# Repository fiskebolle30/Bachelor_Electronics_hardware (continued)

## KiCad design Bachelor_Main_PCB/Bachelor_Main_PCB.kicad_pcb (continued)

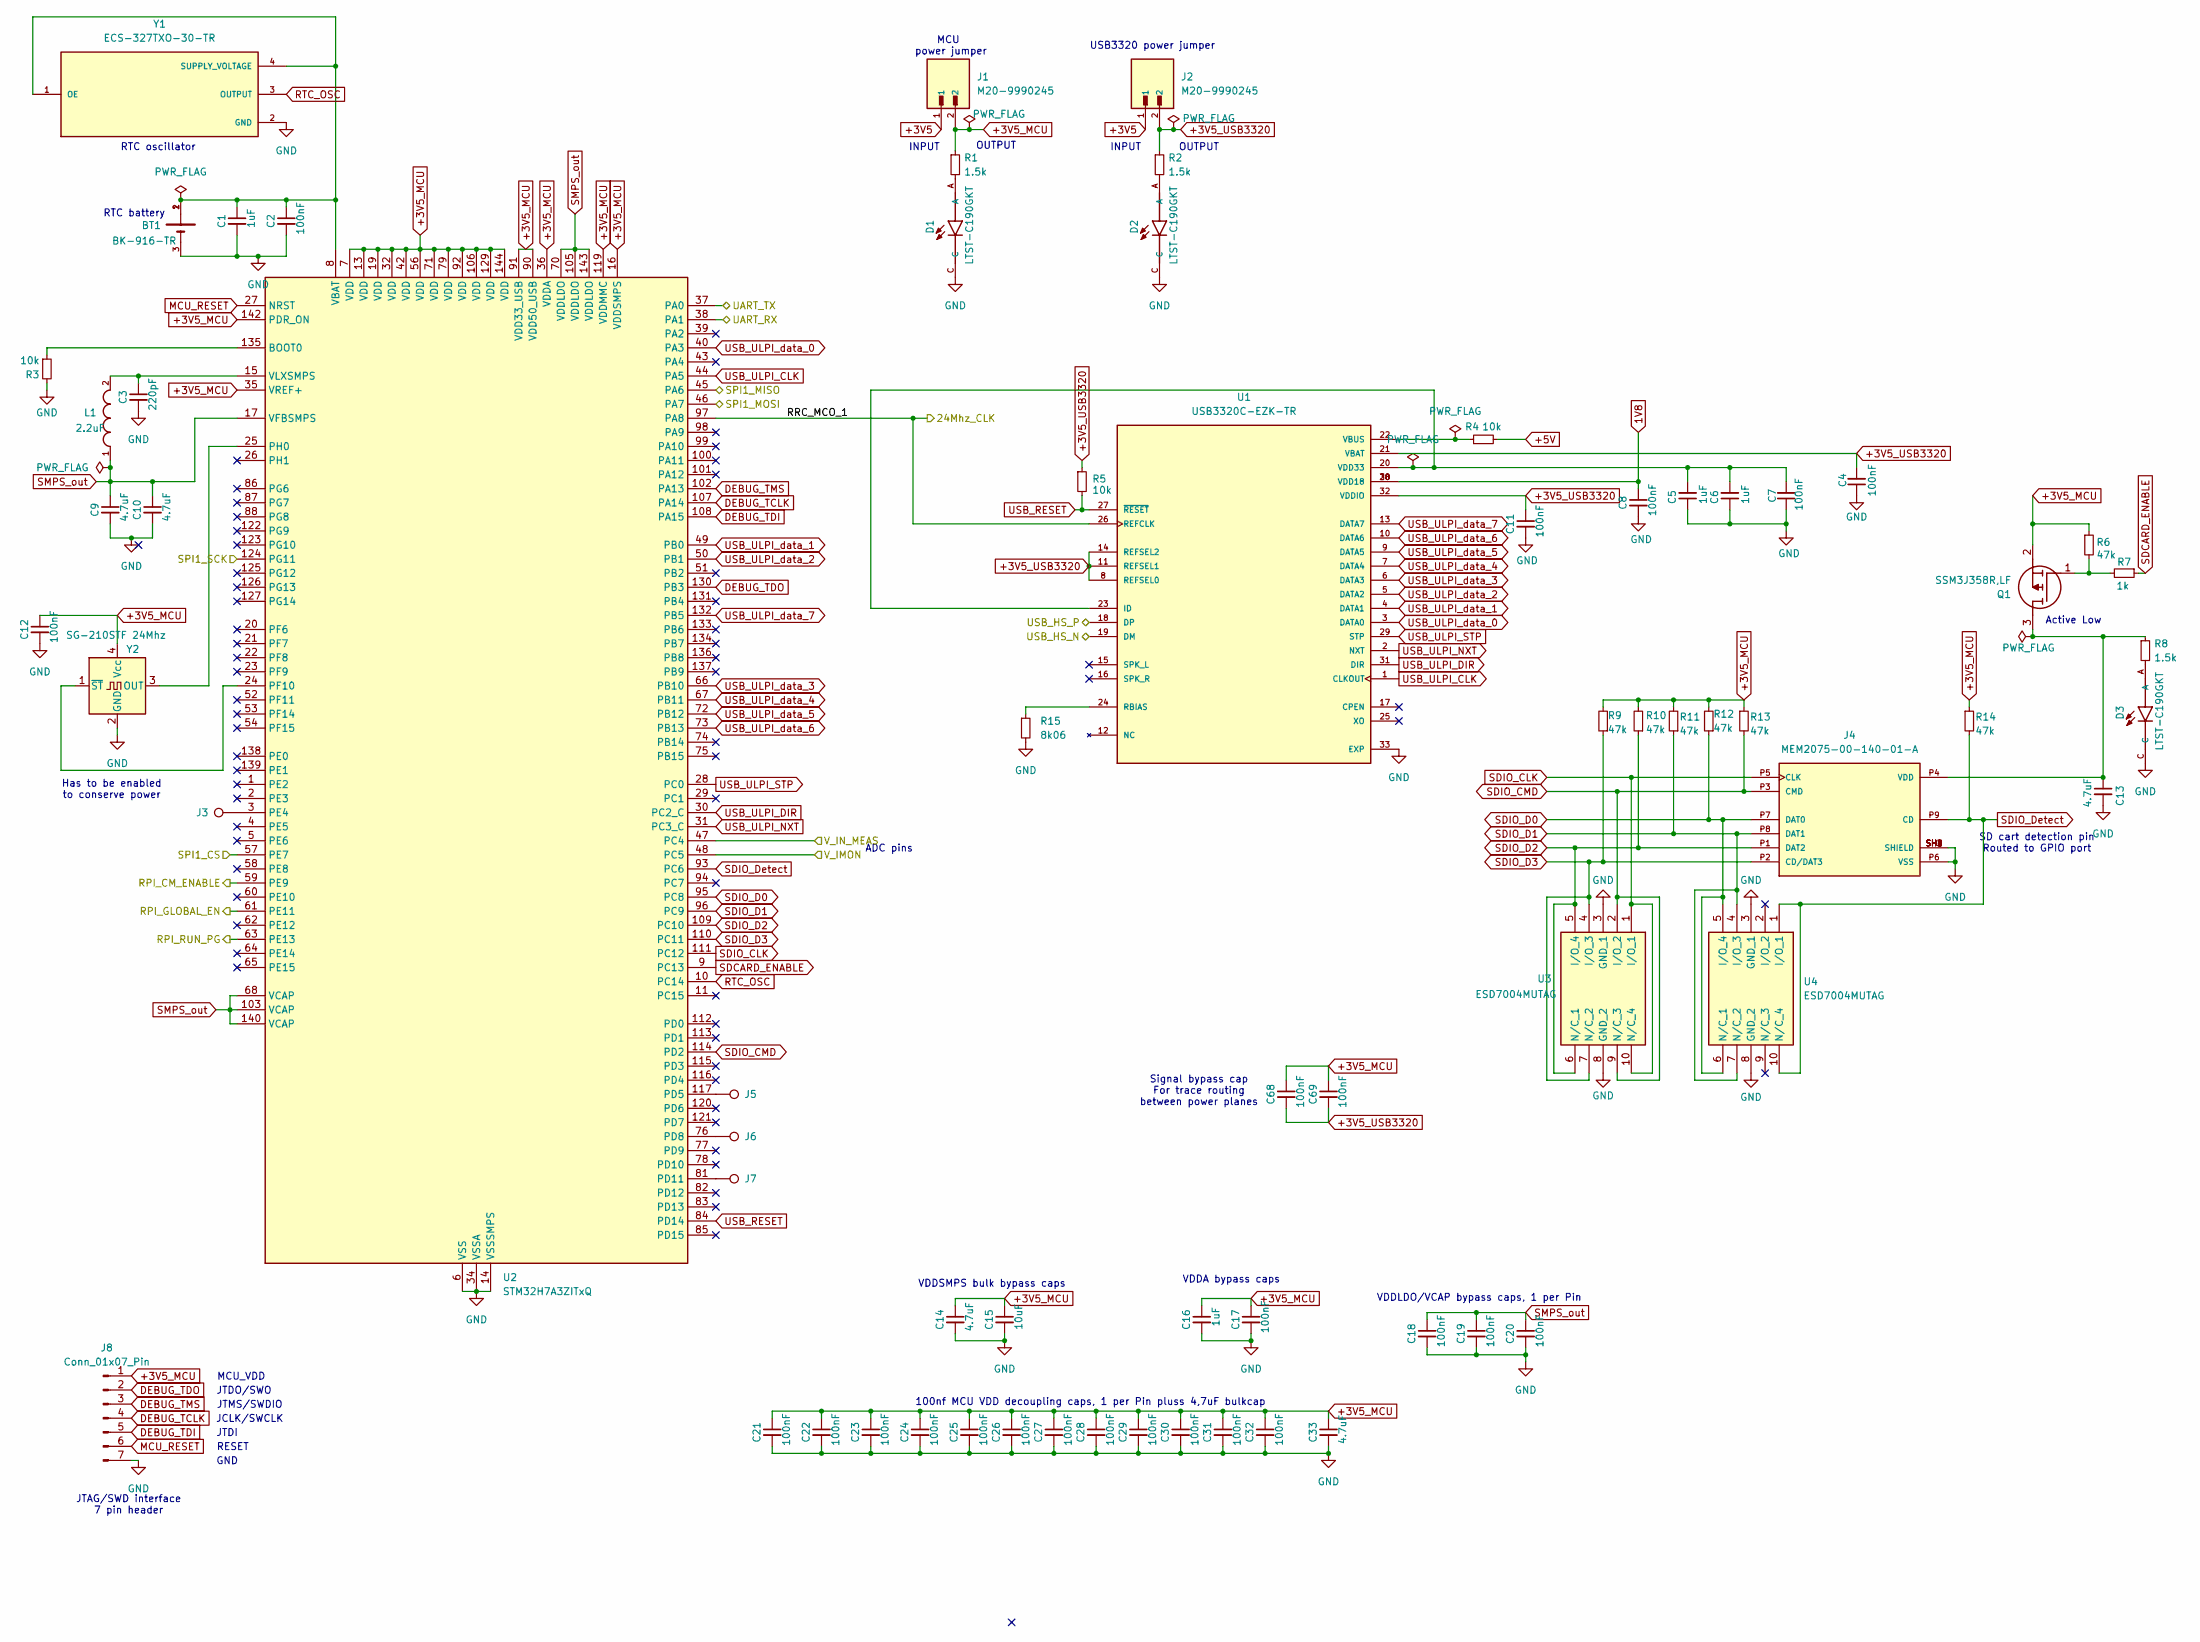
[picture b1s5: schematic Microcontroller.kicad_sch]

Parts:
BT1: BK-916-TR; BAT_BK-916-TR; PARTREV A
C1, C5, C6, C16: 1uF; C_0603_1608Metric; Voltage rating 16v; Part-no CL10B105KO8NNNC
C2, C4, C7, C8, C11, C12, C17, C18, C19, C20, C21, C22, C23, C24, C25, C26, C27, C28, C29, C30, C31, C32, C68, C69: 100nF; C_0603_1608Metric; Voltage rating 50v; Part-no CL10B104KB8NNWC
C3: 220pF; C_0603_1608Metric; Voltage rating 50v; Part-no C0603C221J5GAC7411
C9, C10, C13, C14, C33: 4.7uF; C_0805_2012Metric; Voltage rating 25v; Part-no CL21A475KAQNNNE
C15: 10uF; C_1206_3216Metric; Voltage rating 50v; Part-no CL31B106KBHNNNE
D1, D2, D3: LTST-C190GKT; LEDM1608X80; Part-no LTST-C190GKT
J1, J2: M20-9990245; HARWIN_M20-9990245; PARTREV 14
J3, J5, J6, J7: TestPoint_Pad_D1.0mm
J4: MEM2075-00-140-01-A; GCT_MEM2075-00-140-01-A; PARTREV A
J8: Conn_01x07_Pin; PinHeader_1x07_P2.54mm_Vertical
L1: 2.2uF; INDC2520X120N; Part-no DFE252012P-2R2M=P2
Q1: SSM3J358R,LF; SOTFL95P240X88-3N; Manufacturer_Part_Number SSM3J358R,LF; Mouser Part Number 757-SSM3J358RLF
R1, R2, R8: 1.5k; R_0603_1608Metric
R3, R4, R5: 10k; R_0603_1608Metric; Part-no RC0603FR-0710KL
R6, R9, R10, R11, R12, R13, R14: 47k; R_0603_1608Metric
R7: 1k; R_0603_1608Metric
R15: 8k06; R_0603_1608Metric
U1: USB3320C-EZK-TR; QFN50P500X500X100-33N; PARTREV 05-31-16
U2: STM32H7A3ZITxQ; LQFP-144_20x20mm_P0.5mm; Part-no STM32H7A3ZIT6Q
U3, U4: ESD7004MUTAG; UDFN10_CASE_517BB; Manufacturer_Part_Number ESD7004MUTAG; Mouser Part Number 863-ESD7004MUTAG
Y1: ECS-327TXO-30-TR; OSC_ECS-327TXO-30-TR; PARTREV Rev.2019
Y2: SG-210STF 24Mhz; Oscillator_SMD_SeikoEpson_SG210-4Pin_2.5x2.0mm; Part-no SG-210STF 24Mhz

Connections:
1V8: C8.1, U1.28 (VDD18), U1.30 (VDD18); also elsewhere on the board
+3V5: J1.1, J2.1; also elsewhere on the board
+3V5_MCU: C12.1, C14.1, C15.1, C16.1, C17.1, C21.1, C22.1, C23.1, C24.1, C25.1, C26.1, C27.1, C28.1, C29.1, C30.1, C31.1, C32.1, C33.1, C68.1, C69.1, J1.2, J8.1, Q1.2 (S), R1.1, R6.1, R9.2, R10.2, R11.2, R12.2, R13.1, R14.1, U2.7 (VDD), U2.13 (VDD), U2.16 (VDDSMPS), U2.19 (VDD), U2.32 (VDD), U2.35 (VREF+), U2.36 (VDDA), U2.42 (VDD), U2.56 (VDD), U2.71 (VDD), U2.79 (VDD), U2.90 (VDD50_USB), U2.91 (VDD33_USB), U2.92 (VDD), U2.106 (VDD), U2.119 (VDDMMC), U2.129 (VDD), U2.142 (PDR_ON), U2.144 (VDD), Y2.4 (Vcc)
+3V5_USB3320: C4.2, C11.1, C68.2, C69.2, J2.2, R2.1, R5.1, U1.8 (REFSEL0), U1.11 (REFSEL1), U1.14 (REFSEL2), U1.21 (VBAT), U1.32 (VDDIO)
+5V: R4.2; also elsewhere on the board
/Microcontroller/RPI_CM_ENABLE: U2.59 (PE9); also elsewhere on the board
/Microcontroller/RPI_GLOBAL_EN: U2.61 (PE11); also elsewhere on the board
/Microcontroller/RPI_RUN_PG: U2.63 (PE13); also elsewhere on the board
/Microcontroller/RRC_MCO_1: U1.26 (REFCLK), U2.97 (PA8); also elsewhere on the board
/Microcontroller/UART_RX: U2.38 (PA1); also elsewhere on the board
/Microcontroller/UART_TX: U2.37 (PA0); also elsewhere on the board
/Microcontroller/USB_HS_N: U1.19 (DM); also elsewhere on the board
/Microcontroller/USB_HS_P: U1.18 (DP); also elsewhere on the board
/Microcontroller/V_IMON: U2.48 (PC5); also elsewhere on the board
/Microcontroller/V_IN_MEAS: U2.47 (PC4); also elsewhere on the board
DEBUG_TCLK: J8.4, U2.107 (PA14)
DEBUG_TDI: J8.5, U2.108 (PA15)
DEBUG_TDO: J8.2, U2.130 (PB3)
DEBUG_TMS: J8.3, U2.102 (PA13)
GND: BT1.3, C1.2, C2.2, C3.2, C4.1, C5.1, C6.1, C7.1, C8.2, C9.2, C10.2, C11.2, C12.2, C13.2, C14.2, C15.2, C16.2, C17.2, C18.2, C19.2, C20.2, C21.2, C22.2, C23.2, C24.2, C25.2, C26.2, C27.2, C28.2, C29.2, C30.2, C31.2, C32.2, C33.2, D1.C, D2.C, D3.C, J4.P6 (VSS), J4.SH1 (SHIELD), J4.SH2 (SHIELD), J4.SH3 (SHIELD), J4.SH4 (SHIELD), J8.7, R3.2, R15.2, U1.33 (EXP), U2.6 (VSS), U2.12 (VSS), U2.14 (VSSSMPS), U2.18 (VSS), U2.33 (VSS), U2.34 (VSSA), U2.41 (VSS), U2.55 (VSS), U2.69 (VSS), U2.80 (VSS), U2.89 (VSS), U2.104 (VSS), U2.118 (VSS), U2.128 (VSS), U2.141 (VSS), U3.3 (GND_1), U3.8 (GND_2), U4.3 (GND_1), U4.8 (GND_2), Y1.2 (GND), Y2.2 (GND); also elsewhere on the board
MCU_RESET: J8.6, U2.27 (NRST)
unnamed: D1.A, R1.2
unnamed: D2.A, R2.2
unnamed: D3.A, R8.2
unnamed: C13.1, J4.P4 (VDD), Q1.3 (D), R8.1
unnamed: Q1.1 (G), R6.2, R7.2
unnamed: C5.2, C6.2, C7.2, U1.20 (VDD33), U1.23 (ID)
unnamed: R15.1, U1.24 (RBIAS)
unnamed: R4.1, U1.22 (VBUS)
unnamed: R3.1, U2.135 (BOOT0)
unnamed: J5.1, U2.117 (PD5)
unnamed: J6.1, U2.76 (PD8)
unnamed: J7.1, U2.81 (PD11)
unnamed: J3.1, U2.3 (PE4)
unnamed: U2.24 (PF10), Y2.1 (~ST)
unnamed: U2.25 (PH0), Y2.3 (OUT)
unnamed: BT1.1, BT1.2, C1.1, C2.1, U2.8 (VBAT), Y1.1 (OE), Y1.4 (SUPPLY_VOLTAGE)
unnamed: C3.1, L1.2, U2.15 (VLXSMPS)
RTC_OSC: U2.10 (PC14), Y1.3 (OUTPUT)
SD-pin2: U2.57 (PE7); also elsewhere on the board
SD-pin3: U2.46 (PA7); also elsewhere on the board
SD-pin5: U2.124 (PG11); also elsewhere on the board
SD-pin7: U2.45 (PA6); also elsewhere on the board
SDCARD_ENABLE: R7.1, U2.9 (PC13)
SDIO_CLK: J4.P5 (CLK), U2.111 (PC12), U3.1 (I/O_1), U3.10 (N/C_4)
SDIO_CMD: J4.P3 (CMD), R13.2, U2.114 (PD2), U3.2 (I/O_2), U3.9 (N/C_3)
SDIO_D0: J4.P7 (DAT0), R12.1, U2.95 (PC8), U4.5 (I/O_4), U4.6 (N/C_1)
SDIO_D1: J4.P8 (DAT1), R11.1, U2.96 (PC9), U4.4 (I/O_3), U4.7 (N/C_2)
SDIO_D2: J4.P1 (DAT2), R10.1, U2.109 (PC10), U3.5 (I/O_4), U3.6 (N/C_1)
SDIO_D3: J4.P2 (CD/DAT3), R9.1, U2.110 (PC11), U3.4 (I/O_3), U3.7 (N/C_2)
SDIO_Detect: J4.P9 (CD), R14.2, U2.93 (PC6), U4.1 (I/O_1), U4.10 (N/C_4)
SMPS_out: C9.1, C10.1, C18.1, C19.1, C20.1, L1.1, U2.17 (VFBSMPS), U2.68 (VCAP), U2.70 (VDDLDO), U2.103 (VCAP), U2.105 (VDDLDO), U2.140 (VCAP), U2.143 (VDDLDO)
USB_RESET: R5.2, U1.27 (~RESET), U2.84 (PD14)
USB_ULPI_CLK: U1.1 (CLKOUT), U2.44 (PA5)
USB_ULPI_DIR: U1.31 (DIR), U2.30 (PC2_C)
USB_ULPI_NXT: U1.2 (NXT), U2.31 (PC3_C)
USB_ULPI_STP: U1.29 (STP), U2.28 (PC0)
USB_ULPI_data_0: U1.3 (DATA0), U2.40 (PA3)
USB_ULPI_data_1: U1.4 (DATA1), U2.49 (PB0)
USB_ULPI_data_2: U1.5 (DATA2), U2.50 (PB1)
USB_ULPI_data_3: U1.6 (DATA3), U2.66 (PB10)
USB_ULPI_data_4: U1.7 (DATA4), U2.67 (PB11)
USB_ULPI_data_5: U1.9 (DATA5), U2.72 (PB12)
USB_ULPI_data_6: U1.10 (DATA6), U2.73 (PB13)
USB_ULPI_data_7: U1.13 (DATA7), U2.132 (PB5)

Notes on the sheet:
JTDI
INPUT
SD cart detection pin Routed to GPIO port
RTC oscillator
MCU_VDD
JCLK/SWCLK
OUTPUT
ADC pins
VDDLDO/VCAP bypass caps, 1 per Pin
Signal bypass cap For trace routing between power planes
RESET
Has to be enabled to conserve power
JTDO/SWO
Active Low
100nf MCU VDD decoupling caps, 1 per Pin pluss 4,7uF bulkcap
GND
RTC battery
VDDA bypass caps
JTAG/SWD interface 7 pin header
USB3320 power jumper
MCU power jumper
VDDSMPS bulk bypass caps
JTMS/SWDIO

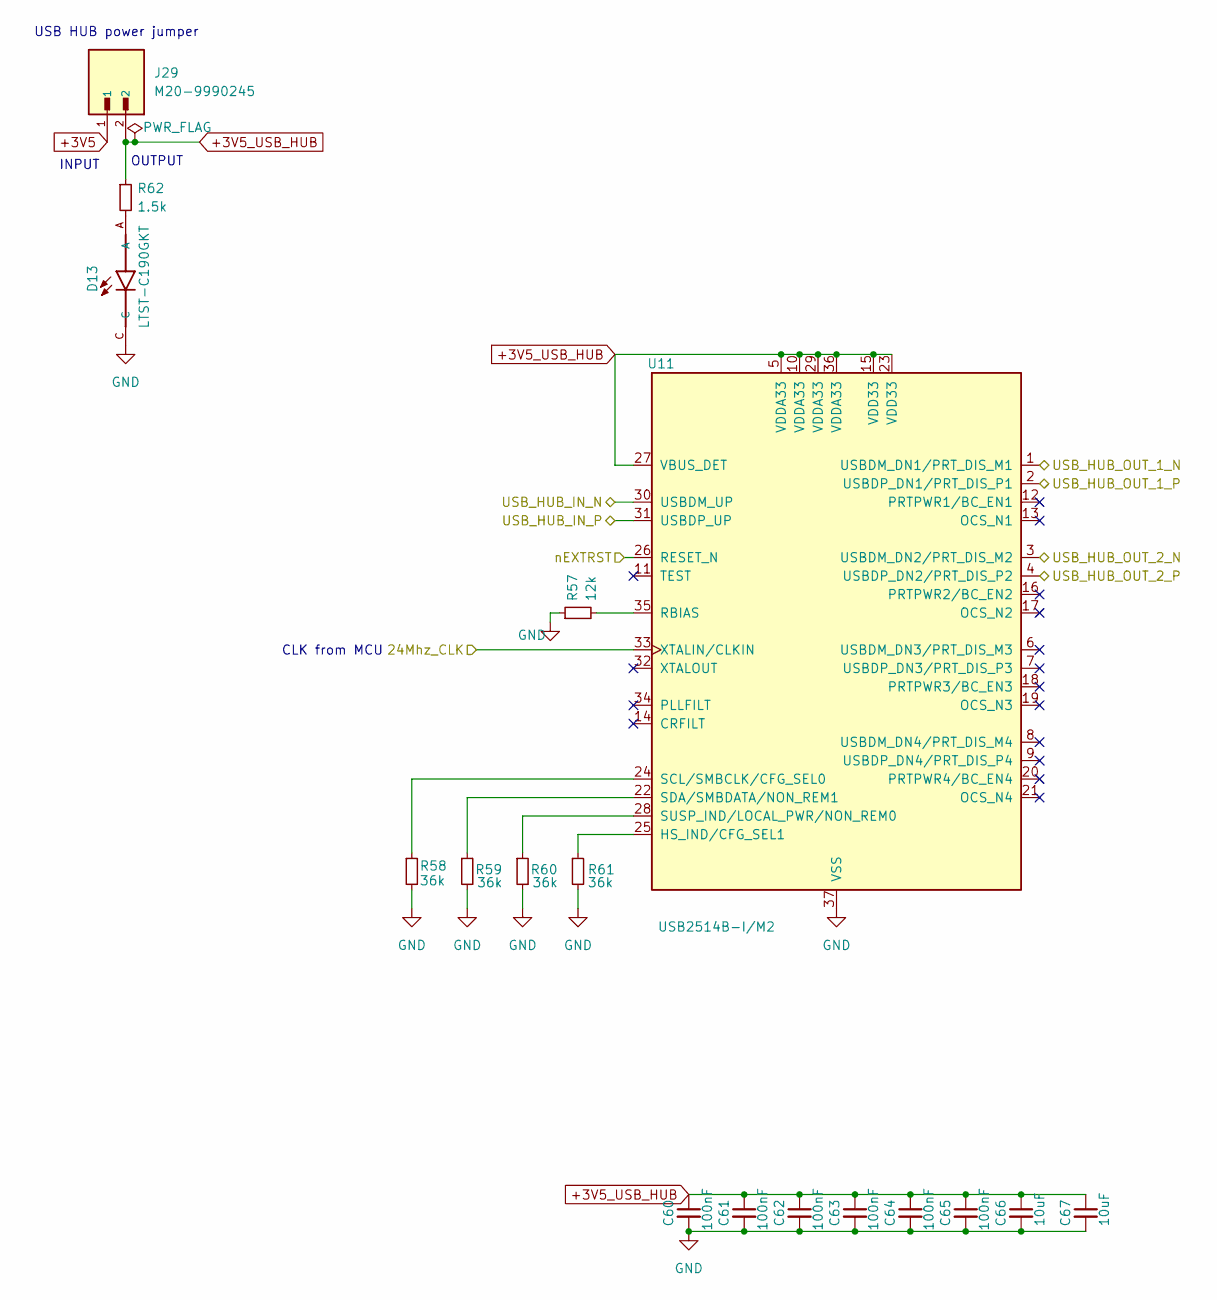
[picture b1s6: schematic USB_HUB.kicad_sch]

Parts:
C60, C61, C62, C63, C64, C65: 100nF; C_0603_1608Metric; Voltage rating 50v; Part-no CL10B104KB8NNWC
C66, C67: 10uF; C_1206_3216Metric; Voltage rating 50v; Part-no CL31B106KBHNNNE
D13: LTST-C190GKT; LEDM1608X80; Part-no LTST-C190GKT
J29: M20-9990245; HARWIN_M20-9990245; PARTREV 14
R57: 12k; R_0603_1608Metric
R58, R59, R60, R61: 36k; R_0603_1608Metric
R62: 1.5k; R_0603_1608Metric
U11: USB2514B-I/M2; QFN-36-1EP_6x6mm_P0.5mm_EP3.7x3.7mm; Part Description USB Hub Controller USB Interface 36-SQF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

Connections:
+3V5: J29.1; also elsewhere on the board
+3V5_USB_HUB: C60.1, C61.1, C62.1, C63.1, C64.1, C65.1, C66.1, C67.1, J29.2, R62.1, U11.5 (VDDA33), U11.10 (VDDA33), U11.15 (VDD33), U11.23 (VDD33), U11.27 (VBUS_DET), U11.29 (VDDA33), U11.36 (VDDA33)
/Microcontroller/RRC_MCO_1: U11.33 (XTALIN/CLKIN); also elsewhere on the board
/Microcontroller/USB_HS_N: U11.1 (USBDM_DN1/PRT_DIS_M1); also elsewhere on the board
/Microcontroller/USB_HS_P: U11.2 (USBDP_DN1/PRT_DIS_P1); also elsewhere on the board
/Raspberry Pi CM 4/USB_HS_N: U11.30 (USBDM_UP); also elsewhere on the board
/Raspberry Pi CM 4/USB_HS_P: U11.31 (USBDP_UP); also elsewhere on the board
/Raspberry Pi CM 4/nEXTRST: U11.26 (RESET_N); also elsewhere on the board
/USB Hub/USB_HUB_OUT_2_N: U11.3 (USBDM_DN2/PRT_DIS_M2); also elsewhere on the board
/USB Hub/USB_HUB_OUT_2_P: U11.4 (USBDP_DN2/PRT_DIS_P2); also elsewhere on the board
GND: C60.2, C61.2, C62.2, C63.2, C64.2, C65.2, C66.2, C67.2, D13.C, R57.1, R58.2, R59.2, R60.2, R61.2, U11.37 (VSS); also elsewhere on the board
unnamed: D13.A, R62.2
unnamed: R61.1, U11.25 (HS_IND/CFG_SEL1)
unnamed: R57.2, U11.35 (RBIAS)
unnamed: R58.1, U11.24 (SCL/SMBCLK/CFG_SEL0)
unnamed: R59.1, U11.22 (SDA/SMBDATA/NON_REM1)
unnamed: R60.1, U11.28 (SUSP_IND/LOCAL_PWR/NON_REM0)

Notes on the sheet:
CLK from MCU
OUTPUT
INPUT
USB HUB power jumper

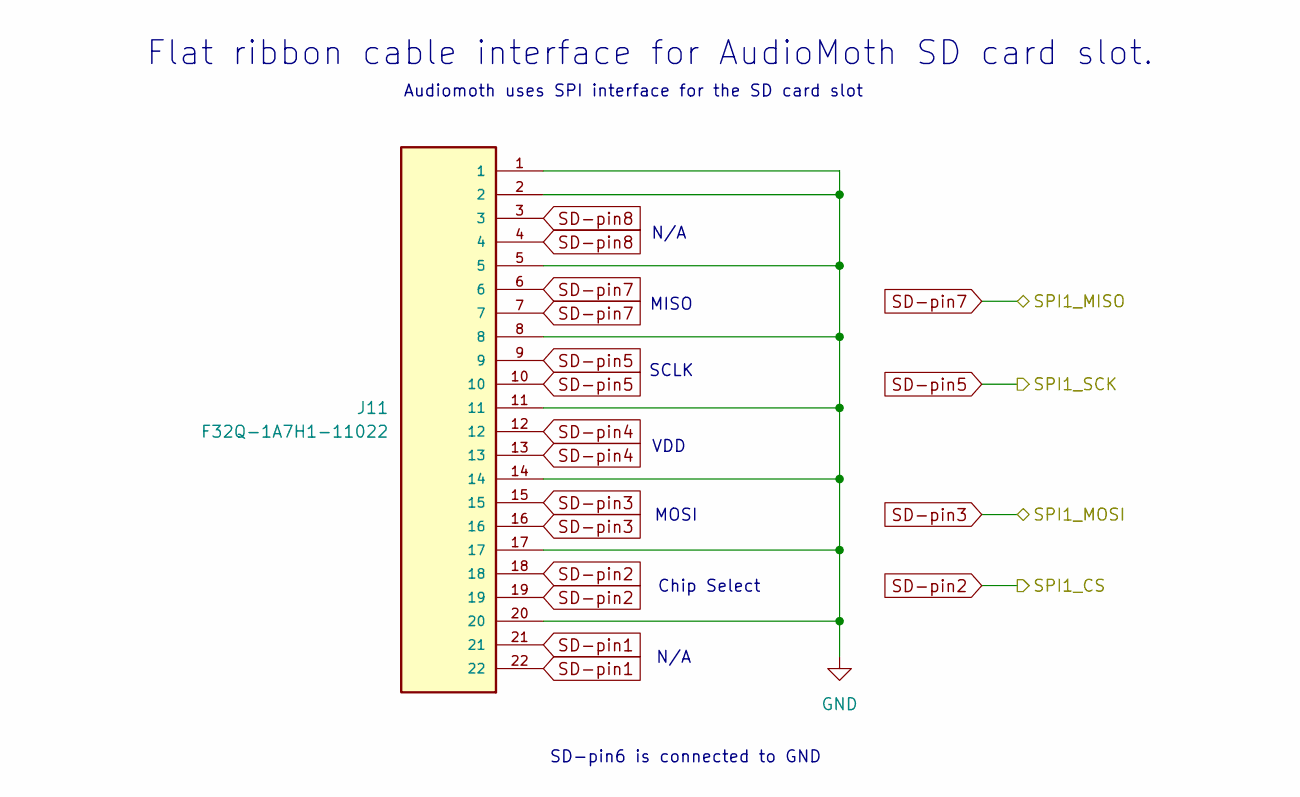
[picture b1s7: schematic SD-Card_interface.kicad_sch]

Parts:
J11: F32Q-1A7H1-11022; AMPHENOL_F32Q-1A7H1-11022; PARTREV D

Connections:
GND: J11.1, J11.2, J11.5, J11.8, J11.11, J11.14, J11.17, J11.20; also elsewhere on the board
SD-pin1: J11.21, J11.22
SD-pin2: J11.18, J11.19; also elsewhere on the board
SD-pin3: J11.15, J11.16; also elsewhere on the board
SD-pin4: J11.12, J11.13
SD-pin5: J11.9, J11.10; also elsewhere on the board
SD-pin7: J11.6, J11.7; also elsewhere on the board
SD-pin8: J11.3, J11.4

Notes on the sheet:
VDD
Flat ribbon cable interface for AudioMoth SD card slot.
SCLK
N/A
N/A
MISO
Chip Select
MOSI
Audiomoth uses SPI interface for the SD card slot
SD-pin6 is connected to GND

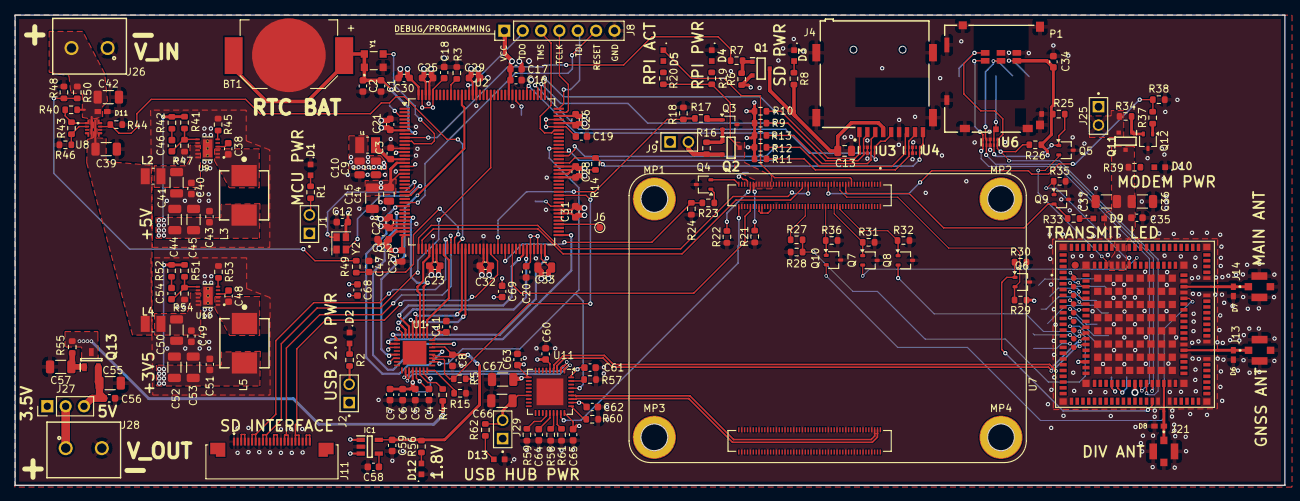
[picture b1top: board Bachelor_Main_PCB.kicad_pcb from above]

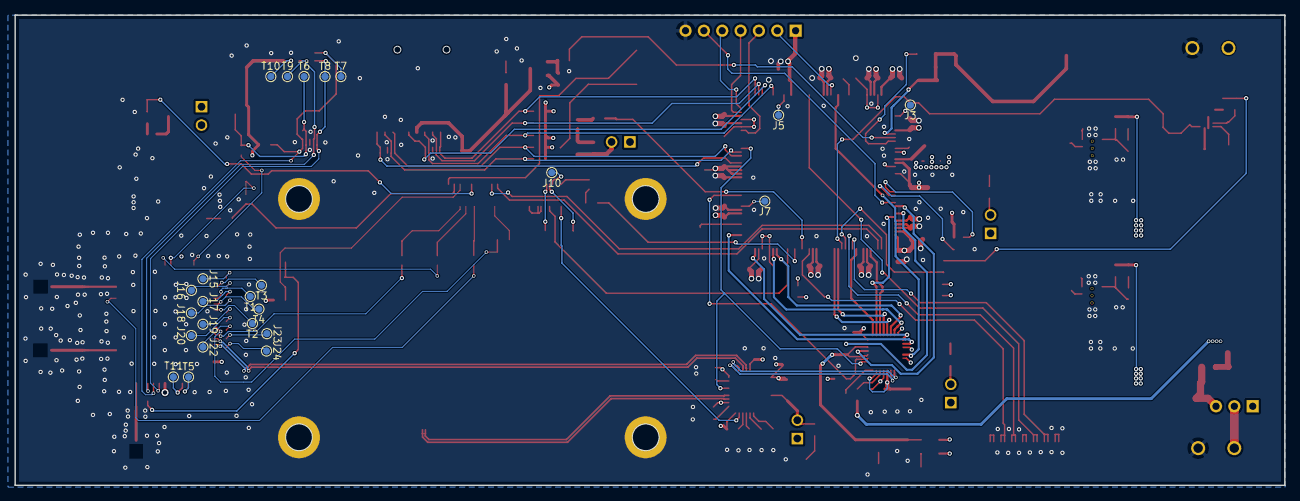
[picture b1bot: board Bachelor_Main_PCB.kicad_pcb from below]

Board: 4 copper layers, 175.8 x 65.1 mm, 224 parts (24 on the bottom side), 161 nets.

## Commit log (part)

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2025-03-04 innitial creation of KiCad project
    With 1 resistor 0603 standard size to be used
2025-03-14 Add Ribon cable connector
    F32Q-1A7H1-11022
2025-03-14 add gitignore
2025-03-14 Update gitignore removed gitignore files from repo
2025-03-14 Add RPI cm and route all Ribon cable pins correctly
2025-03-14 Updated ribon cable pins
2025-03-17 Add GND to RPI CM
2025-03-17 Add Spacers for RPI CM and created separate hierarchical sheets
2025-03-17 Add Sierra Wireless modem and 100pin RPI CM connectors
2025-03-17 Fix 100 pin RPI CM connector 3D model
    part of RPI CM 3d model now
2025-03-19 Add STM32 and 3d model. Made power suply sheet
2025-03-19 Small changes
    Just moved some components
2025-03-21 Add STM32 3D modell
2025-03-21 småtteri
2025-03-24 Add SIM card holder
2025-03-24 Add USB-Tranciever
2025-03-25 ULPI global lables
2025-03-26 Add Y1 oscillator to the USB3320
    24Mhz oscillator for the USB tranciever
2025-03-28 Add Bypass cap USB3320
2025-03-28 Routing some MCU pins
2025-03-28 Add more bypass caps
2025-03-31 Fix bypass cap routing
2025-03-31 Add Rbias resisstor to USB3320
2025-03-31 Route ID pin on USB3320, Fix 0603 footprint on resistors
2025-03-31 Add RPI_5v pin
2025-03-31 USB3320 CPEN is NC!
2025-03-31 Add USB3320 Reset pin pullup
2025-03-31 USB3320 Reset connected to PD14
2025-03-31 Route RPI USB
    PS: we need a USB hub
2025-04-01 Add 1x2header library
2025-04-01 Add MCU, USB3320 and USB_HUB power jumpers
2025-04-01 Add 2,2uF inductor to MCU
2025-04-01 Add MCU VDD caps
2025-04-01 VDDLDO add bypass caps
2025-04-02 Add more bypass caps to MCU
2025-04-02 add BK-916 rtc battery holder
2025-04-02 VDDUSB headers together
2025-04-02 PDR_on to VDD
2025-04-04 Add RTC oscillator
2025-04-04 ADD JTAG 7pin header
2025-04-07 Renamed JTAG_ pins to DEBUG_
    Due to it being both JTAG and SWD (serial wire debug)
2025-04-07 More concise labeling of DEBUG pins
2025-04-07 MODEM power connections
2025-04-07 Add MODEM testpoints
2025-04-07 Add SIM card circuit and ESD supression
2025-04-07 Fix anotation of "J" designators and routed ESD suppression on Modem
2025-04-07 ADD mosfet controls from BUGG MODEM
2025-04-07 Add all MODEM signals
2025-04-07 Add modem safe power remove
2025-04-07 Add routing between hierarchal sheets modem and RPI
2025-04-07 Switched 3,3 for 3,5_MODEM for Q11 and Q9 circuits
2025-04-08 Add MODEM_3V5_EN mosfet
    Controlls the power supply to the modem from the RPI GPIO7
2025-04-08 Change MODEM_3V5_EN mosfet to P-channel type SSM3j358R
2025-04-08 ADD MODEM_3V5_EN signal inverter
2025-04-08 Renamed wring MODEM_3V7_en to 3V5
2025-04-08 Add USB HUB of type USB2514B-i/M2
    Same as RPI CM 4 IO board
2025-04-08 Add Vcc to Y1
2025-04-08 Add 24Mhz clock to USB hub. same as USB tranciever
2025-04-08 Add HUB bypass caps
2025-04-09 ADD USBHUB Reset pin
2025-04-09 USB HUB done
2025-04-09 Fix hierarchal sheet naming for USB hub
2025-04-09 Routed Sheeets
2025-04-09 Add SD CARD pullups
2025-04-09 SD CARD ESD TVS Diodes
2025-04-09 Add cdcard to MCU connections(except detect pin)
2025-04-09 MAIN_RF TVS diode and routed SDIO_DETECT
2025-04-09 ADD UFL antenna connectors
2025-04-09 Started on PSU sheet
2025-04-11 Add GNSS antenna Connector
    Which is DNP but can be nice in future revision/ implementation
2025-04-11 add LM 73100 ideal diode
2025-04-11 Added RIMON + R1,R2,R3 to Ideal diode circuit
2025-04-12 Add RPI to MCU UART communication
2025-04-12 Add RPI power Switch MOSFET, Fix direction of power switch MOSFETs
2025-04-12 Switched RX and TX for UART connection
    so that the TX from RPI go into RX on MCU
2025-04-12 Add 1,8v regulator
    LD3985M18R
2025-04-12 updated 1,8v global lables
2025-04-12 Added text to SD audiomoth interface
2025-04-13 Make correct stackup and add 90ohm differential pair usb
2025-04-13 Made corecct 90ohm diff pair net settings
    Calculated with Saturn PCB toolkit. Width 0.23 and space 1,5
2025-04-13 Make all usb lines part of DP_90ohm nettclass
2025-04-13 55ohm ULPI Net made and assigned
2025-04-13 Add RPI CM enable pin to MCU sheet
2025-04-13 Add SDcard enable VCC pin with PMOS
2025-04-13 Fixed schematic of SDcard enable pin
2025-04-14 Add audiomoth to MCU SPI
2025-04-14 Add Vin sampling and route V_IN and V_IMON to MCU sheet
2025-04-14 add PC4 and PC5 as V_IN and V_IMON
2025-04-14 Add LMR51450 switch mode regulator.
2025-04-14 Remove RPI CM power on mosfet. Replaced with EN pin to PSU
    the pin is now routed instead to the LMR51450 converter ENABLE pin.
2025-04-14 add pulldown to PSU EN pin
2025-04-14 Add voltage select divider
2025-04-14 add 4,7uH switchmode inductor
2025-04-14 add 3,3uH inductor for 3,5v and add Rff and Cff to FB pin
2025-04-14 Add series inductors to switch mode convertors. Add screw terminal
    For the audiomoth power.
2025-04-15 Reinstated Mosfet RPI_CM_ENABLE controll
    instead of enable pin on switch mode controller. this way the audiomoth can use the 5v supply with the capacitor multiplier.
2025-04-15 Add BC817 and complete capacitance multiplier
2025-04-15 add more LEDs
2025-04-15 connect RPI GPIO_VREF to internal 3,3v regulator
2025-04-15 Add LED to SD card vcc pin
2025-04-16 Achematic review changes. Smal ones. Replaced TX_ON LED
2025-04-16 Add cap multiplier simulation
2025-04-16 Add 24Mhz to MCU
2025-04-16 Routed 24Mhz
2025-04-16 added 100nF to 24Mhz oscillators
2025-04-16 Add 3 pin header to select which PSU for the AudioMoth
2025-04-16 Add LMR51450FNDRRR chip note
    For the PFM and FPWM modes
2025-04-16 Changed RTC clock to 3.0v model from 3,3v model
2025-04-17 Add correct 47uF partno and footpring
2025-04-17 Add correct 10uF partno
2025-04-17 EXchange 2,2uF for 2x1uF caps to reduce bom. add 4,7uF partno
2025-04-17 Add signal inverter to RPIcm enable pin.
    In order to protect MCU against 5v input on GPIO pin.
2025-04-17 add 10k to Q3
2025-04-17 Add 24Mhz gpio controll
2025-04-17 Remove 24Mhz oscillators from hub and tranciever
    Replaced with trace to PA8 pin which is the internaly supplied oscillator from the MCU
2025-04-17 Updated the "Part-no" field in the symbol field table for all components
2025-04-17 All resistors and capacitors correct footprints
2025-04-17 Add 1% tolerance field to high tolerance resistors
2025-04-17 Add Part-no to all caps and replaced 15pF on bugg with 33pF
2025-04-17 Add pulldown to power switch mosfets
2025-04-17 Changed ideal diode resistors to 23v cutoff instead of 20v cutoff
2025-04-17 Add Part-no for all resistors with 1% tolerance
2025-04-17 Fix resistor nameing
2025-04-17 Standardized on "." for decimal spaces
2025-04-17 removed old RPI_5v enable
2025-04-21 Add boot0 tie to ground and footprint to L1
2025-04-21 Add RPI activity led to pin 21
2025-04-21 Add RPI pins: WL_pins, RUN_PG, RPIBOOT and GLOBAL_EN with a mosfet
    the MOSFET to protect against 5v in to MCU
2025-04-21 Add RPI_RUNPG and GLOBAL_EN pins to MCU sheet and Root
2025-04-21 Removed Modem_safe_PWR_remove pin.
    was potential use for the MCU but would require level shifters and would not add any functionality ass the RPI controls the Modem anyway.
2025-04-21 Fix all DRC errors and warnings
    except not connected pins still unrouted to MCU
2025-04-21 Småpirk
2025-04-21 Add connections to all MCU unrouted pins
2025-04-21 Imported components from schematic to PCB and Reanotat all designators
    THis means every designator is now different and the references made prior no longer applies
2025-04-21 Added 3d model to sd card slot
2025-04-22 Changed SIM card connector to SF70S006VBAR2000
    the other one was not available
2025-04-22 add some 3D models
2025-04-22 changed symbol libraries to kiprjmod from 3dmodel
2025-04-22 changed footprint library the same way and added 3D-models to all components
2025-04-22 layouot decoupling caps to MCU
2025-04-22 Rearanged components on layout
2025-04-22 Rotated BAT
2025-04-23 arrange modem components
2025-04-23 More arrange modem comp
2025-04-23 arrange SIM card components. Fix DSW1 and DSW2 circuit.
2025-04-23 Add custom nettie for Waveguide. Aligned modem connectors
2025-04-23 Change footprint of RPICM to better courtyard
    so as to not cause errors with components underneath
2025-04-23 place modem testpoints
2025-04-23 add gnd plane and fixed MCU bypass cap trace error
2025-04-23 Updated gnd planes
2025-04-23 MODEM testppoints and gnd fill
2025-04-23 something
2025-04-24 Sim card testpoints
2025-04-24 complete Modem testpoints
2025-04-24 Route SIMcard and 3v5 modem
2025-04-24 SD card pwr. legends for leds
2025-04-24 Rearanged MCU
2025-04-24 USB3320 arrange CAPS
2025-04-24 Fixed polygons are now filled zones
2025-04-24 continue PSU layout
2025-04-24 Completed PSU layout
2025-04-24 Duplicate PSU layout
2025-04-24 Fixed Batery paste layer and shrunk PCB
2025-04-24 Layout ideal diode
2025-04-24 Changed V_IN on adc mcu sense pin to V_VIN_MEAS
2025-04-24 change IDEAL DIODE
2025-04-25 Text from meeting with julia
2025-04-25 Fix VIN_MEAS voltage divider
2025-04-25 resized R7 and R6 from 10k each
2025-04-25 Same as last
2025-04-25 smal fixes
2025-04-25 Update SMPS for MCU
2025-04-25 Fix RPI 3d model.
2025-04-25 add SMPS plane under MCU
2025-04-25 route VCAP bypass
2025-04-25 further bypass caping
2025-04-25 no cap further cap
2025-04-25 Add LED to USB_HUB
2025-04-25 Routed USBhub/transiever
2025-04-25 Modem fixing
2025-04-25 Route SIM data
2025-04-25 Ready for Diff pair
2025-04-25 Route MODEM DIFF
2025-04-25 Route DIFF
2025-04-26 Route last USB
2025-04-26 Fully route USB hub
2025-04-26 route all HUB BYPASS CAPS
2025-04-26 Route al ULPI
2025-04-26 Route SD card
2025-04-26 RPI power
2025-04-26 RPI power after crash
2025-04-26 Align LEDS
2025-04-26 Align leds MORE
2025-04-26 arrange PSU
2025-04-26 arange PSU
2025-04-26 Route more PSU
2025-04-26 PSU 5v rail
2025-04-26 Route debug
2025-04-26 start Audiomoth SD routing
2025-04-26 Completed SD routing
2025-04-26 Complete SD routing
2025-04-27 fixup traces
2025-04-27 Start routing RPI
2025-04-27 Done modem routing
2025-04-27 Route UART
2025-04-27 Done route RPI
2025-04-27 Fixing up clock signal
2025-04-27 More routing
2025-04-27 Anoying routing
2025-04-27 The routing continues to never stop
2025-04-27 You probably wont believe this but more routing
2025-04-27 THis may come as a shook but there has been EVEN more routing
2025-04-27 The fabric of reality is tearing, the routed traces are trying to hold it together
2025-04-27 The traces have ascended beyond our plane of existence
2025-04-27 The traces cry out in unison, the third impact is upon us
2025-04-27 Humanity endures countless eons of subjugation from the trace lord
2025-04-27 Until, a hero emerges. He fights against the empire inciting revolution
2025-04-27 In a final stand for the fate of the world the hero vanquishes the lord
2025-04-27 However the wounds sustained during the fight were to severe
2025-04-27 The hero is carried to the great willow tree where he grew up
2025-04-27 He rests underneath sunny skies, never shall we see his likeness again
2025-04-27 Add 2 100nF between MCU and Transceiver power planes for return path
2025-04-27 Routing and ad silkprint
2025-04-27 Silkprint
2025-04-27 RATSNEST IS DONE!!!
2025-04-27 GND VIAS
2025-04-27 EDGE vias stitching
2025-04-27 Add GND to USB Chips
2025-04-27 GND vias and fix footprint vias
2025-04-28 GND vias and resized power zones
2025-04-28 Add mounting holes
2025-04-28 Start DRC check
2025-04-28 Continue DRC
2025-04-28 CHange RPICM solder mask expansion for pads
2025-04-28 Update mouting holes to m2.5 to use same screws as RPICM
2025-04-28 Complete DRC
2025-04-28 Final commit. All DRC done. All silkprint good. Ready for ordering
    So long and thanks for all the fish
2025-04-28 Add final fiducial and layer check section
2025-04-28 Update vias on switch modes to not be bad
2025-04-28 Fixed switch mode CHIP GND
2025-04-28 Add MPN to all resistors. Only missing pinheaders
2025-04-29 removed duplicate 3d model for STM32
2025-04-30 Made 2 3d model step files for the PCB. one simple one complex
2025-05-04 Removed part-no in schematics
2025-05-18 Update page settings for all sheets. Add title, revision, date, etc.
2025-05-18 Tidy up schematics
2025-05-19 Made interactive HTML bom
2025-05-19 Update regulator PN to the PFM version, add notes for next revision.
2025-05-23 Changes to the capacitive multiplier Simulation files
